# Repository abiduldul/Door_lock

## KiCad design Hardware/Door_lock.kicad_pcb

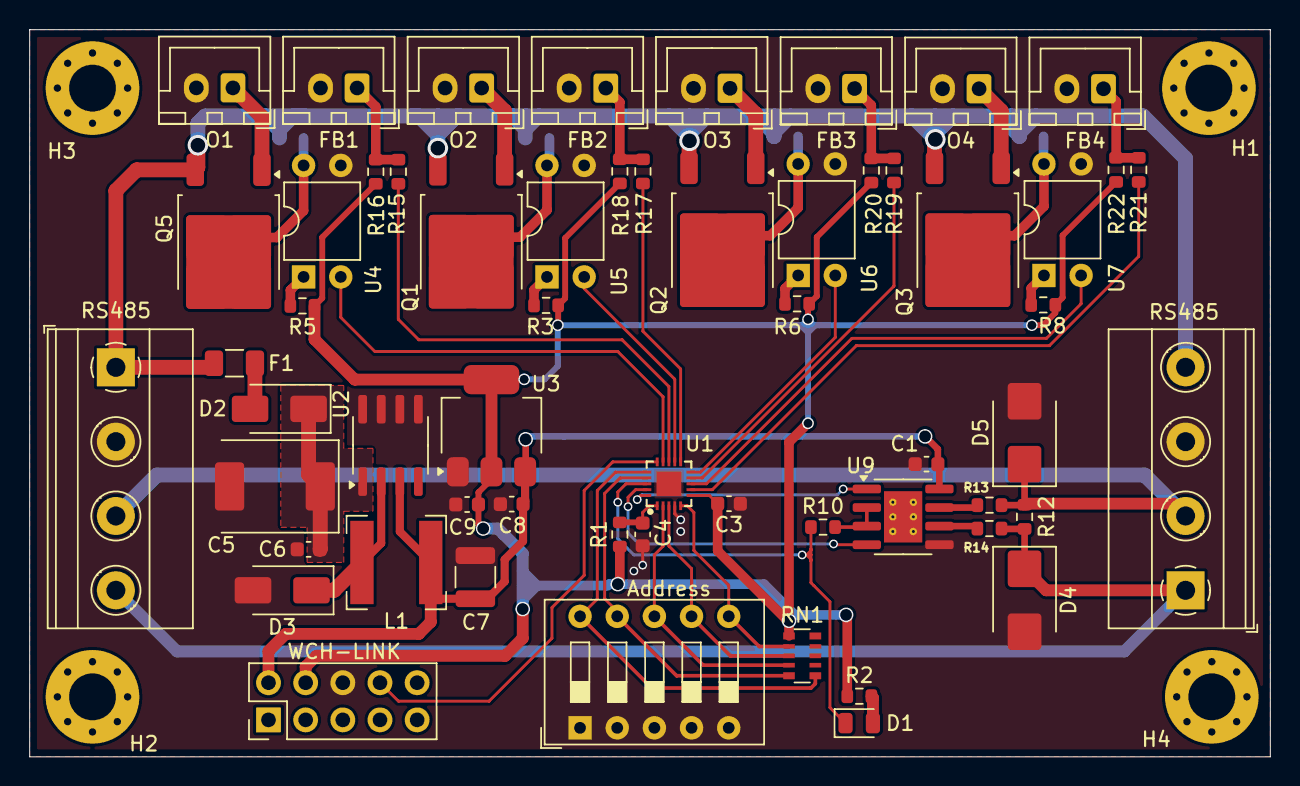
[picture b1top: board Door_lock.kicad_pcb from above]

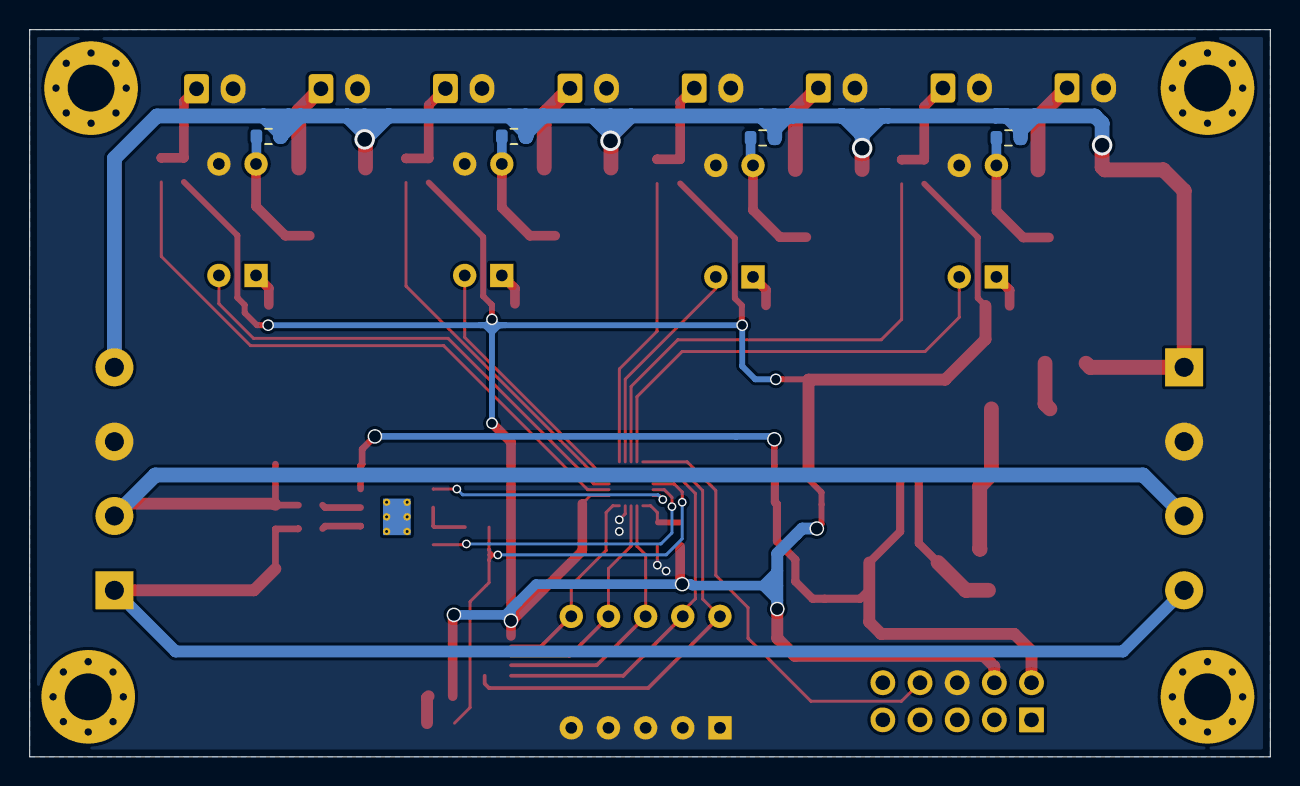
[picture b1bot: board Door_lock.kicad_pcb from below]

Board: 4 copper layers, 84.8 x 49.7 mm, 66 parts (4 on the bottom side), 47 nets.

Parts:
Address: SW_DIP_x05; SW_DIP_SPSTx05_Slide_9.78x14.88mm_W7.62mm_P2.54mm
C1, C3, C4: 100nF; C_0603_1608Metric
C5: 470uF; CP_EIA-7361-438_AVX-U
C6: 10nF; C_0603_1608Metric
C7: 100uF; C_1210_3225Metric
C8, C9: 10uF; C_0603_1608Metric
D1: GREEN; LED_0805_2012Metric
D2: M7; D_SMA
D3: B5817; D_SMA
D4, D5: ESD9B5.0ST5G; D_SMB
F1: Fuse; Fuse_1206_3216Metric
FB1, FB2, FB3, FB4: Conn_01x02; JST_XH_B2B-XH-A_1x02_P2.50mm_Vertical
H1, H2, H3, H4: MountingHole; MountingHole_3.2mm_M3_Pad_Via
L1: 68uH; L_Bourns-SRN6028
O1, O2, O3, O4: Conn_01x02; JST_XH_B2B-XH-A_1x02_P2.50mm_Vertical
Q1, Q2, Q3, Q5: PMOS; TO-252-2
R1: 10K; R_0603_1608Metric
R2: 2K2; R_0603_1608Metric
R3, R5, R6, R8, R10: 560; R_0603_1608Metric
R4, R7, R9, R11, R16, R18, R20, R22: 10k; R_0603_1608Metric
R12: 120; R_0603_1608Metric
R13, R14: 10; R_0603_1608Metric
R15, R17, R19, R21: 1k; R_0603_1608Metric
RN1: R_Network05; R_Array_Convex_5x0603
RS485, RS485#2: Conn_01x04; TerminalBlock_Phoenix_MKDS-1,5-4-5.08_1x04_P5.08mm_Horizont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
U1: CH32V003F4U6; QFN-20_L3.0-W3.0-P0.40-TL-EP1.7
U2: XL1509-5.0; SOIC-8_3.9x4.9mm_P1.27mm
U3: AMS1117-3.3; SOT-223-3_TabPin2
U4, U5, U6, U7: PC817; DIP-4_W7.62mm
U9: MAX485E; SOIC-8-1EP_3.9x4.9mm_P1.27mm_EP2.62x3.51mm_ThermalVias
WCH-LINK: Conn_02x05_Odd_Even; PinHeader_2x05_P2.54mm_Vertical

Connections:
+3V3: C3.2, C9.2, R1.1, R2.1, R3.1, R5.1, R6.1, R8.1, R16.2, R18.2, R20.2, R22.2, RN1.1 (common), U1.6 (VDD), U3.2 (VO), WCH-LINK.4
+5V: C1.2, C7.1, C8.2, L1.2, U2.3 (FB), U3.3 (VI), U9.8 (VCC), WCH-LINK.2
+12V: F1.1, Q1.3 (S), Q2.3 (S), Q3.3 (S), Q5.3 (S), R4.1, R7.1, R9.1, R11.1, RS485.1, RS485#2.4
A: D4.1 (A1), R12.1, R14.1, RS485.4, RS485#2.1
B: D5.1 (A1), R12.2, R13.1, RS485.3, RS485#2.2
FB1: R15.1, U1.13 (PC6/MOSI/T1CH1CH3N_)
FB2: R17.1, U1.11 (PC4/A2/T1CH4/MCO)
FB3: R19.1, U1.9 (PC2/SCL/URTS/T1BKIN)
FB4: R21.1, U1.7 (PC0/T2CH3/UTX_)
GND: Address.1, Address.2, Address.3, Address.4, Address.5, C1.1, C3.1, C4.1, C5.2, C6.2, C7.2, C8.1, C9.1, D3.2 (A), D4.2 (A2), D5.2 (A2), FB1.2, FB2.2, FB3.2, FB4.2, O1.2, O2.2, O3.2, O4.2, RS485.2, RS485#2.3, U1.4 (VSS), U1.21 (VSS), U2.5 (GND), U2.6 (GND), U2.7 (GND), U2.8 (GND), U3.1 (GND), U4.3, U5.3, U6.3, U7.3, U9.5 (GND), WCH-LINK.6
IO1: U1.14 (PC7/MISO/T1CH2_), U4.2
IO2: U1.12 (PC5/SCK/T1ETR/T2CH1ETR_), U5.2
IO3: U1.10 (PC3/T1CH3/T1CH1N_), U6.2
IO4: U1.8 (PC1/SDA/NSS/T2CH4_), U7.2
unnamed: D1.2 (A), R2.2
unnamed: D2.2 (A), F1.2
unnamed: C5.1, C6.1, D2.1 (K), U2.1 (VIN)
unnamed: D3.1 (K), L1.1, U2.2 (OUT)
unnamed: O2.1, Q1.1 (D)
unnamed: O3.1, Q2.1 (D)
unnamed: O1.1, Q5.1 (D)
unnamed: O4.1, Q3.1 (D)
unnamed: FB1.1, R15.2, R16.1
unnamed: FB2.1, R17.2, R18.1
unnamed: FB3.1, R19.2, R20.1
unnamed: FB4.1, R21.2, R22.1
unnamed: Q1.2 (G), R4.2, U5.4
unnamed: Q2.2 (G), R7.2, U6.4
unnamed: Q3.2 (G), R9.2, U7.4
unnamed: Q5.2 (G), R11.2, U4.4
unnamed: R3.2, U5.1
unnamed: R5.2, U4.1
unnamed: R6.2, U6.1
unnamed: R8.2, U7.1
unnamed: C4.2, R1.2, U1.1 (PD7/NRST/T2CH4)
unnamed: R14.2, U9.6 (A)
unnamed: R13.2, U9.7 (B)
unnamed: R10.2, U9.2 (~RE), U9.3 (DE)
PD4: D1.1 (K), R10.1, U1.18 (PD4/A7/UCK/T2CH1ETR)
RX: U1.20 (PD6/A6/URX), U9.1 (RO)
SWDIO: U1.15 (PD1/SWIO/AETR2), WCH-LINK.8
TX: U1.19 (PD5/A5/UTX), U9.4 (DI)
addr1: Address.10, RN1.6 (R5), U1.16 (PD2/A3/T1CH1/T2CH3_)
addr2: Address.9, RN1.5 (R4), U1.17 (PD3/A4/T2CH2/AETR)
addr3: Address.8, RN1.4 (R3), U1.2 (PA1/OSCI/A1)
addr4: Address.7, RN1.3 (R2), U1.3 (PA2/OSCO/A0/T1CH2N)
addr5: Address.6, RN1.2 (R1), U1.5 (PD0/T1CH1N/OPN1)

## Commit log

2024-06-04 add schematic
2024-06-06 update hardware design
